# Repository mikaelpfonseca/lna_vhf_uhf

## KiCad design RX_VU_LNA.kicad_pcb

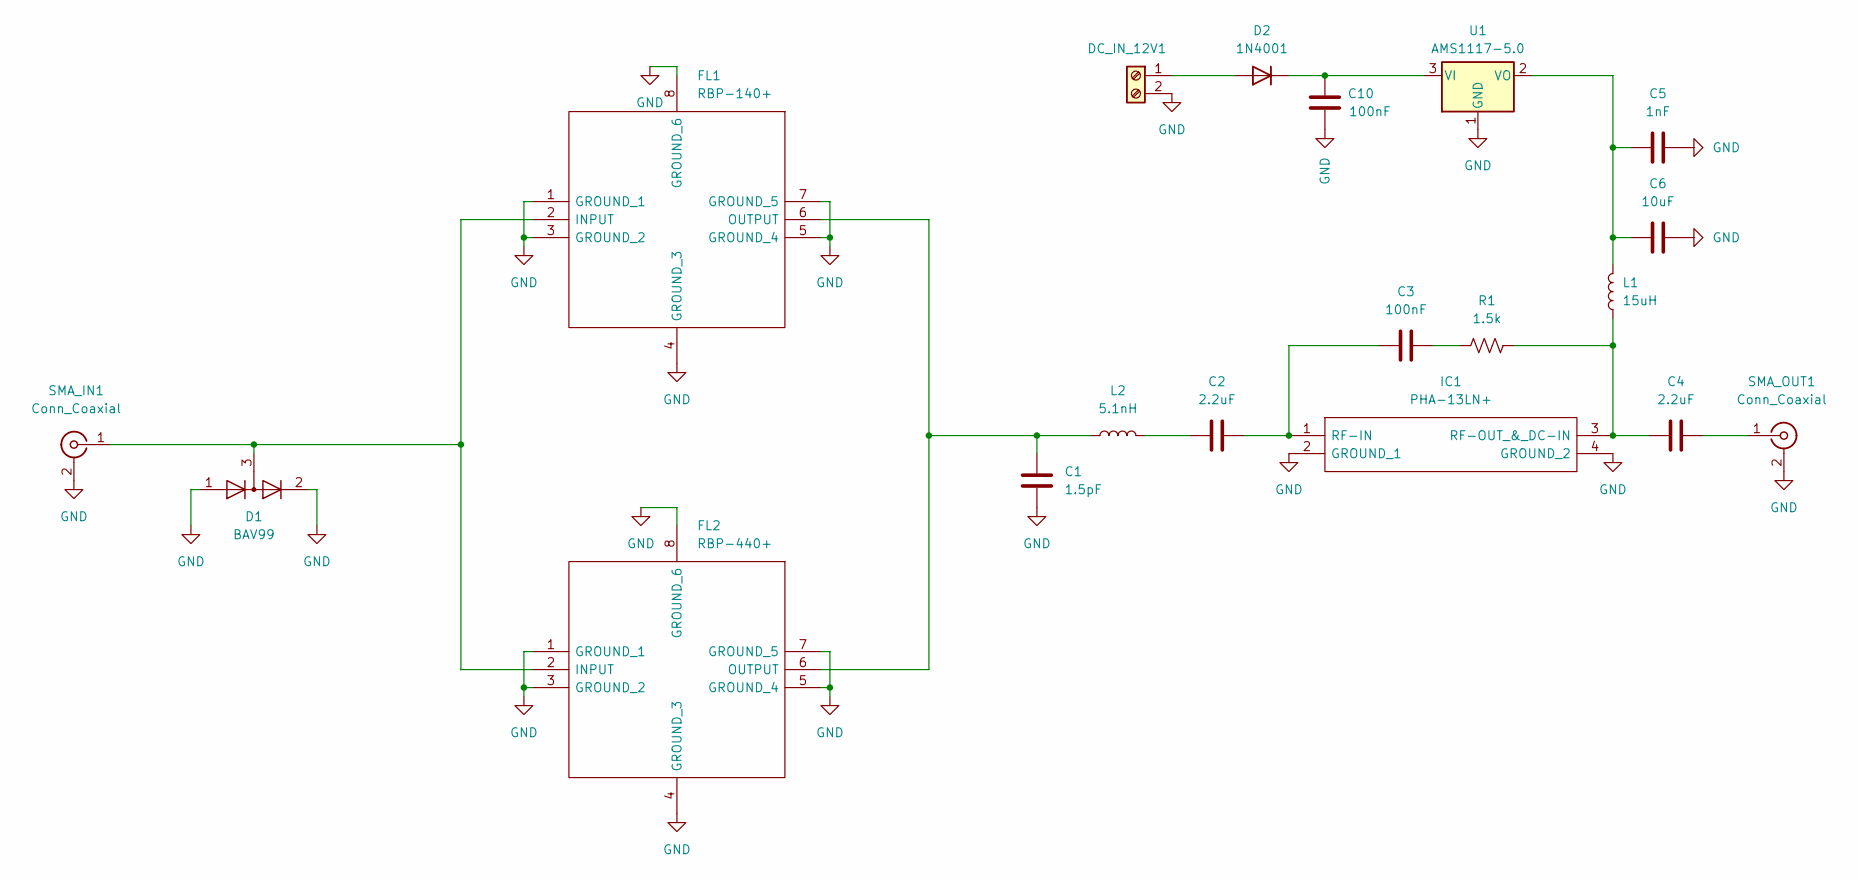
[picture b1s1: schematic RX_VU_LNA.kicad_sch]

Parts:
C1: 1.5pF; C_0805_2012Metric
C2, C4: 2.2uF; C_0805_2012Metric
C3, C10: 100nF; C_0805_2012Metric
C5: 1nF; C_0805_2012Metric
C6: 10uF; C_0805_2012Metric
D1: BAV99; SOT-23
D2: 1N4001; D_SOD-123
DC_IN_12V1: Screw_Terminal_01x02; TerminalBlock_bornier-2_P5.08mm
FL1: RBP-140+; RBP140; Mouser Part Number 139-RBP-140
FL2: RBP-440+; RBP140; Mouser Part Number 139-RBP-140
IC1: PHA-13LN+; PHA13LN; Mouser Part Number 139-PHA-13LN
L1: 15uH; L_0805_2012Metric
L2: 5.1nH; L_0805_2012Metric
R1: 1.5k; R_0805_2012Metric
SMA_IN1: Conn_Coaxial; SMA_Amphenol_132289_EdgeMount
SMA_OUT1: Conn_Coaxial; SMA_Amphenol_132289_EdgeMount
U1: AMS1117-5.0; SOT-223-3_TabPin2

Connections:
GND: C1.2, C5.2, C6.2, C10.2, D1.1 (K), D1.2 (A), DC_IN_12V1.2, FL1.1 (GROUND_1), FL1.3 (GROUND_2), FL1.4 (GROUND_3), FL1.5 (GROUND_4), FL1.7 (GROUND_5), FL1.8 (GROUND_6), FL2.1 (GROUND_1), FL2.3 (GROUND_2), FL2.4 (GROUND_3), FL2.5 (GROUND_4), FL2.7 (GROUND_5), FL2.8 (GROUND_6), IC1.2 (GROUND_1), IC1.4 (GROUND_2), SMA_IN1.2 (Ext), SMA_OUT1.2 (Ext), U1.1 (GND)
unnamed: C1.1, FL1.6 (OUTPUT), FL2.6 (OUTPUT), L2.1
unnamed: C2.1, L2.2
unnamed: C2.2, C3.1, IC1.1 (RF-IN)
unnamed: C3.2, R1.1
unnamed: C4.1, IC1.3 (RF-OUT_&_DC-IN), L1.1, R1.2
unnamed: C4.2, SMA_OUT1.1 (In)
unnamed: C5.1, C6.1, L1.2, U1.2 (VO)
unnamed: C10.1, D2.1 (K), U1.3 (VI)
unnamed: D1.3 (K), FL1.2 (INPUT), FL2.2 (INPUT), SMA_IN1.1 (In)
unnamed: D2.2 (A), DC_IN_12V1.1

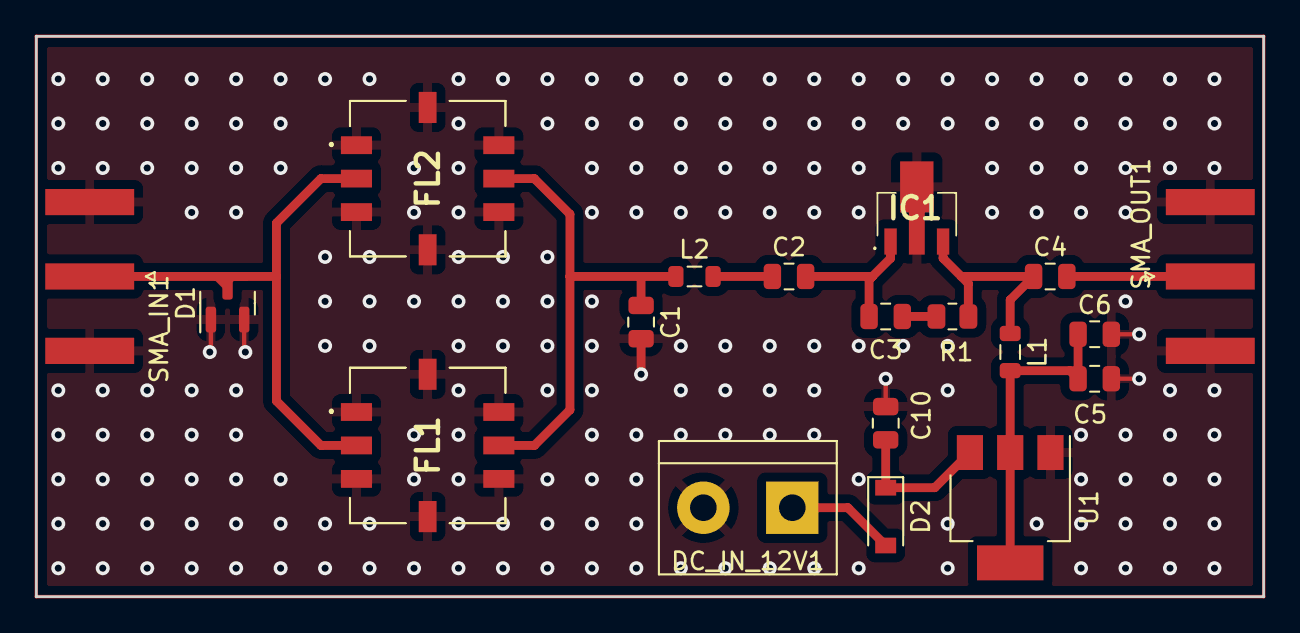
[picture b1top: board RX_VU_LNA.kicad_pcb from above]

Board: 2 copper layers, 70.1 x 32.0 mm, 19 parts (0 on the bottom side), 11 nets.
